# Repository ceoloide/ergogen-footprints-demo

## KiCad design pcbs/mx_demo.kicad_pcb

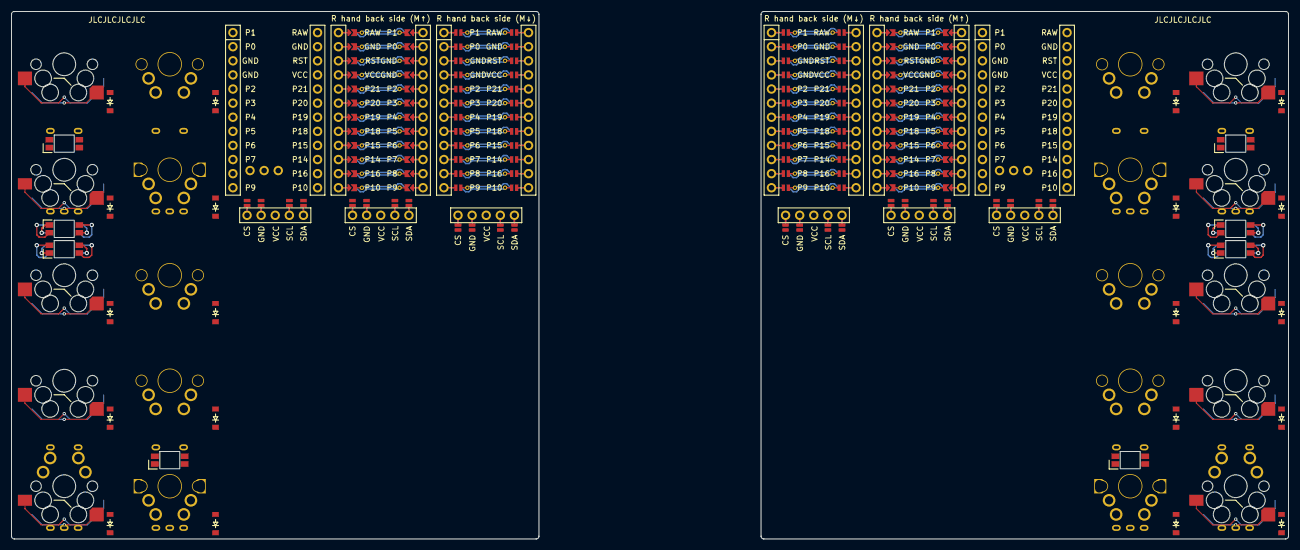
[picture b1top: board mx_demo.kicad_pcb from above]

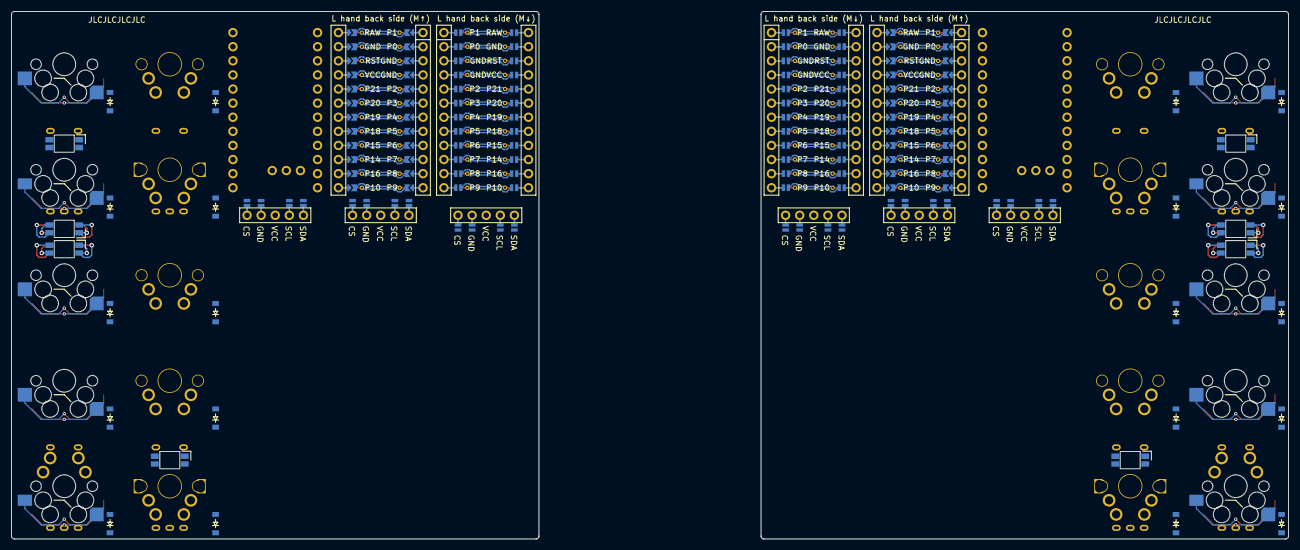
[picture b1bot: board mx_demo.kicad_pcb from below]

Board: 2 copper layers, 230.0 x 95.0 mm, 88 parts (48 on the bottom side), 85 nets.

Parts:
D1, D2, D3, D4, D5, D6, D7, D8, D9, D10, D11, D12, D13, D14, D15, D16, D17, D18, D19, D20, D21, D22, D23, D24, D25, D26, D27, D28, D29, D30, D31, D32, D33, D34, D35, D36, D37, D38, D39, D40: diode_tht_sod123
DISP1, DISP2, DISP3, DISP4, DISP5, DISP6: display_nice_view
LED1, LED2, LED3, LED4, LED5, LED6: led_SK6812mini-e (per-key, reversible)
LED7, LED8: led_SK6812mini-e (underglow, reversible)
MCU1, MCU2, MCU3, MCU4, MCU5, MCU6: mcu_supermini_nrf52840
RE1, RE2, RE3, RE4, RE5, RE6, RE7, RE8: rotary_encoder_ec11_ec12
S1, S2, S3, S4, S5, S6, S7, S8, S9, S10, S11, S12, S13, S14, S15, S16, S17, S18, S19, S20: switch_mx

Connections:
CS: DISP1.10, DISP1.20, DISP2.10, DISP2.20, DISP3.14, DISP3.24, DISP4.14, DISP4.24, DISP5.14, DISP5.24, DISP6.14, DISP6.24
DISP1_1: DISP1.1, DISP1.14, DISP1.27
DISP1_2: DISP1.2, DISP1.15, DISP1.26
DISP1_4: DISP1.4, DISP1.16, DISP1.25
DISP1_5: DISP1.5, DISP1.17, DISP1.24
DISP2_1: DISP2.1, DISP2.14, DISP2.27
DISP2_2: DISP2.2, DISP2.15, DISP2.26
DISP2_4: DISP2.4, DISP2.16, DISP2.25
DISP2_5: DISP2.5, DISP2.17, DISP2.24
DISP3_1: DISP3.1, DISP3.10, DISP3.23
DISP3_2: DISP3.2, DISP3.11, DISP3.22
DISP3_4: DISP3.4, DISP3.12, DISP3.21
DISP3_5: DISP3.5, DISP3.13, DISP3.20
DISP4_1: DISP4.1, DISP4.10, DISP4.23
DISP4_2: DISP4.2, DISP4.11, DISP4.22
DISP4_4: DISP4.4, DISP4.12, DISP4.21
DISP4_5: DISP4.5, DISP4.13, DISP4.20
DISP5_1: DISP5.1, DISP5.10, DISP5.23
DISP5_2: DISP5.2, DISP5.11, DISP5.22
DISP5_4: DISP5.4, DISP5.12, DISP5.21
DISP5_5: DISP5.5, DISP5.13, DISP5.20
DISP6_1: DISP6.1, DISP6.10, DISP6.23
DISP6_2: DISP6.2, DISP6.11, DISP6.22
DISP6_4: DISP6.4, DISP6.12, DISP6.21
DISP6_5: DISP6.5, DISP6.13, DISP6.20
GND: DISP1.11, DISP1.21, DISP2.11, DISP2.21, DISP3.15, DISP3.25, DISP4.15, DISP4.25, DISP5.15, DISP5.25, DISP6.15, DISP6.25, LED1.3, LED2.3, LED3.3, LED4.3, LED5.3, LED6.3, LED7.3, LED8.3, MCU1.102, MCU1.121, MCU1.122, MCU2.102, MCU2.121, MCU2.122, MCU3.103, MCU3.104, MCU3.123, MCU4.103, MCU4.104, MCU4.123, MCU5.2, MCU5.21, MCU5.22, MCU6.2, MCU6.21, MCU6.22, RE1.B, RE2.B, RE3.B, RE4.B, RE5.B, RE6.B, RE7.B, RE8.B
LED: LED1.4, LED2.4
LED_2: LED3.4, LED4.4, LED5.4, LED6.4, LED7.2, LED8.2
LED_3: LED3.2, LED4.2, LED5.2, LED6.2
LED_U_1: LED1.2, LED2.2, LED7.4, LED8.4
P0: MCU1.123, MCU2.123, MCU3.102, MCU4.102, MCU5.23, MCU6.23
P1: MCU1.124, MCU2.124, MCU3.101, MCU4.101, MCU5.24, MCU6.24
P2: MCU1.120, MCU2.120, MCU3.105, MCU4.105, MCU5.20, MCU6.20
P3: MCU1.119, MCU2.119, MCU3.106, MCU4.106, MCU5.19, MCU6.19
P4: MCU1.118, MCU2.118, MCU3.107, MCU4.107, MCU5.18, MCU6.18
P5: MCU1.117, MCU2.117, MCU3.108, MCU4.108, MCU5.17, MCU6.17
P6: MCU1.116, MCU2.116, MCU3.109, MCU4.109, MCU5.16, MCU6.16
P7: MCU1.115, MCU2.115, MCU3.110, MCU4.110, MCU5.15, MCU6.15
P8: MCU1.114, MCU2.114, MCU3.111, MCU4.111, MCU5.14, MCU6.14
P9: MCU1.113, MCU2.113, MCU3.112, MCU4.112, MCU5.13, MCU6.13
P10: MCU1.112, MCU2.112, MCU3.113, MCU4.113, MCU5.12, MCU6.12
P14: MCU1.110, MCU2.110, MCU3.115, MCU4.115, MCU5.10, MCU6.10
P15: MCU1.109, MCU2.109, MCU3.116, MCU4.116, MCU5.9, MCU6.9
P16: MCU1.111, MCU2.111, MCU3.114, MCU4.114, MCU5.11, MCU6.11
P18: MCU1.108, MCU2.108, MCU3.117, MCU4.117, MCU5.8, MCU6.8
P19: MCU1.107, MCU2.107, MCU3.118, MCU4.118, MCU5.7, MCU6.7
P20: MCU1.106, MCU2.106, MCU3.119, MCU4.119, MCU5.6, MCU6.6
P21: MCU1.105, MCU2.105, MCU3.120, MCU4.120, MCU5.5, MCU6.5
P101: MCU5.25, MCU6.25
P102: MCU5.26, MCU6.26
P107: MCU5.27, MCU6.27
RAW: MCU1.101, MCU2.101, MCU3.124, MCU4.124, MCU5.1, MCU6.1
RE_A: RE1.A, RE2.A, RE3.A, RE4.A, RE5.A, RE6.A, RE7.A, RE8.A
RE_C: RE1.C, RE2.C, RE3.C, RE4.C, RE5.C, RE6.C, RE7.C, RE8.C
RST: MCU1.103, MCU2.103, MCU3.122, MCU4.122, MCU5.3, MCU6.3
SCL: DISP1.12, DISP1.22, DISP2.12, DISP2.22, DISP3.16, DISP3.26, DISP4.16, DISP4.26, DISP5.16, DISP5.26, DISP6.16, DISP6.26
SDA: DISP1.13, DISP1.23, DISP2.13, DISP2.23, DISP3.17, DISP3.27, DISP4.17, DISP4.27, DISP5.17, DISP5.27, DISP6.17, DISP6.27
VCC: DISP1.3, DISP2.3, DISP3.3, DISP4.3, DISP5.3, DISP6.3, LED1.1, LED2.1, LED3.1, LED4.1, LED5.1, LED6.1, LED7.1, LED8.1, MCU1.104, MCU2.104, MCU3.121, MCU4.121, MCU5.4, MCU6.4
c1: RE1.S1, RE2.S1, RE3.S1, RE4.S1, S1.1, S2.1, S3.1, S4.1, S5.1, S6.1, S7.1, S8.1, S9.1, S10.1
c1_r1: D5.2, D25.2, S1.2
c1_r2: D4.2, D24.2, RE2.S2, S3.2
c1_r3: D3.2, D23.2, S5.2
c1_r4: D2.2, D22.2, S7.2
c1_r5: D1.2, D21.2, RE1.S2, S9.2
c2: S11.1, S12.1, S13.1, S14.1, S15.1, S16.1, S17.1, S18.1, S19.1, S20.1
c2_r1: D10.2, D30.2, S11.2
c2_r2: D9.2, D29.2, S13.2
c2_r3: D8.2, D28.2, S15.2
c2_r4: D7.2, D27.2, S17.2
c2_r5: D6.2, D26.2, S19.2
mirror_c1_r1: D15.2, D35.2, S2.2
mirror_c1_r2: D14.2, D34.2, RE4.S2, S4.2
mirror_c1_r3: D13.2, D33.2, S6.2
mirror_c1_r4: D12.2, D32.2, S8.2
mirror_c1_r5: D11.2, D31.2, RE3.S2, S10.2
mirror_c2_r1: D20.2, D40.2, S12.2
mirror_c2_r2: D19.2, D39.2, S14.2
mirror_c2_r3: D18.2, D38.2, S16.2
mirror_c2_r4: D17.2, D37.2, S18.2
mirror_c2_r5: D16.2, D36.2, S20.2
r1: D5.1, D10.1, D15.1, D20.1, D25.1, D30.1, D35.1, D40.1
r2: D4.1, D9.1, D14.1, D19.1, D24.1, D29.1, D34.1, D39.1
r3: D3.1, D8.1, D13.1, D18.1, D23.1, D28.1, D33.1, D38.1
r4: D2.1, D7.1, D12.1, D17.1, D22.1, D27.1, D32.1, D37.1
r5: D1.1, D6.1, D11.1, D16.1, D21.1, D26.1, D31.1, D36.1

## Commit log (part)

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2024-02-18 Setting up the config file
2024-02-18 Add package-lock.json after installing npm
2024-02-18 Update PCB name
2024-02-18 Add switches and diodes
2024-02-19 Exclude lock files
2024-02-19 Update footprints submodule
2024-02-19 Add components to test
2024-02-19 Refresh output
2024-02-21 Update footprints library
2024-02-21 Add some rotation and shift to test footprints
2024-03-02 Update footprints
2024-03-03 Adjust the position of a few components
2024-03-03 Add nice_nano with only required jumpers
2024-03-06 Slightly adjust power switch
2024-03-06 Add alternate power switch behavior
2024-03-07 Increase size of reverse hotswap pad
2024-03-07 Update LED wirign and position
2024-03-07 Add reset buttons
2024-03-22 Add SSD1306 footprint
2024-03-29 Add mirror options to test footprints
2024-03-29 Add mirror to board to test footprints
2024-03-29 Add `resist` on diodes to keep them asymmetric
2024-03-29 Update TRRS positions and related footprint library
2024-03-30 Update TRRS footprint pinout and library
2024-03-30 Update reset switch position
2024-04-02 Update footprint library and reference for MCU / Display
2024-04-04 Update nice!nano footprint
2024-04-06 Update footprints library and add copper fill zone
2024-04-07 Update footprints library and use extra pins in nice!view
2024-04-08 Add ergogen logo
2024-04-10 Update packages and footprints library
2024-04-11 Updgrade to KiCad 8 PCB template
2024-04-13 Update min Ergogen version
2024-04-15 Update footprints library and add plated mounting hole
2024-04-15 Make Nice!Nano reversible
2024-04-15 Update footprints library and make one MCU not reverse mount (MCU Up)
2024-04-15 Add point debugger
2024-04-15 Update footprints library to include Molex Pico EzMate battery connector
2024-04-24 Update ergogen to latest develop version (includes `point` ref in footprints)
2024-04-24 Update footprints library and configuration
2024-05-08 Update footprints and demo board
2024-05-23 Update various aspects of the build pipeline and its outputs
2024-10-21 Update to the latest ergogen-footprints version
2024-11-11 Update output
2024-11-12 Update build scripts
2024-11-12 Update build pipeline and folder location (fix #1)
2024-11-22 Rename demo board for Choc v1/v2 and add MX demo board
2024-11-26 Update footprint library
2024-11-26 Split demo board in Choc and MX variants
2024-11-26 Update assets
2024-12-02 Update @ceoloide's footprints library
2024-12-04 Update @ceoloide's footprint library
